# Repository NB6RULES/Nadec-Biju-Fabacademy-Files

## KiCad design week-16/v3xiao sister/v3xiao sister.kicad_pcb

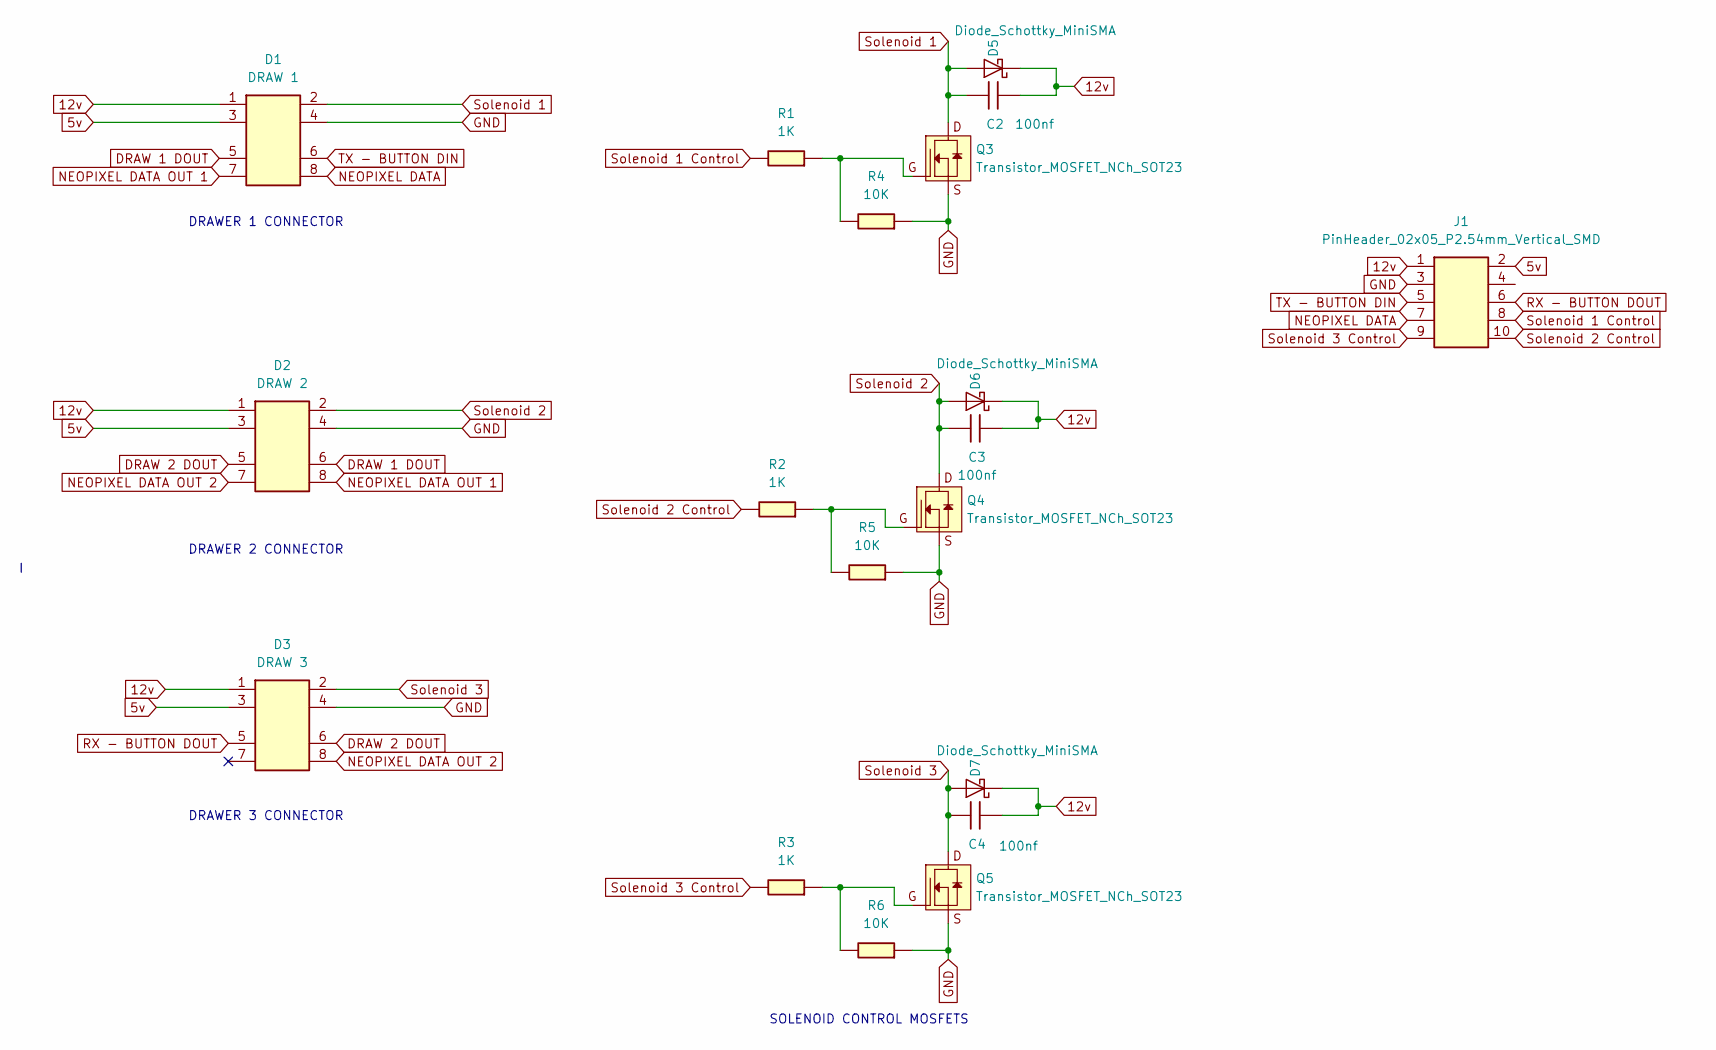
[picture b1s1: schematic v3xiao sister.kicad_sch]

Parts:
C2, C3, C4: 100nf; C_1206
D1: DRAW 1; PinHeader_02x04_P2.54mm_Vertical_SMD
D2: DRAW 2; PinHeader_02x04_P2.54mm_Vertical_SMD
D3: DRAW 3; PinHeader_02x04_P2.54mm_Vertical_SMD
D5, D6, D7: Diode_Schottky_MiniSMA
J1: PinHeader_02x05_P2.54mm_Vertical_SMD
Q3, Q4, Q5: Transistor_MOSFET_NCh_SOT23; SOT-23-3
R1, R2, R3: 1K; R_1206
R4, R5, R6: 10K; R_1206

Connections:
5v: D1.3, D2.3, D3.3, J1.2
12v: C2.2, C3.2, C4.2, D1.1, D2.1, D3.1, D5.1 (K), D6.1 (K), D7.1 (K), J1.1
DRAW 1 DOUT: D1.5, D2.6
DRAW 2 DOUT: D2.5, D3.6
GND: D1.4, D2.4, D3.4, J1.3, Q3.2 (S), Q4.2 (S), Q5.2 (S), R4.2, R5.2, R6.2
NEOPIXEL DATA: D1.8, J1.7
NEOPIXEL DATA OUT 1: D1.7, D2.8
NEOPIXEL DATA OUT 2: D2.7, D3.8
unnamed: Q3.1 (G), R1.2, R4.1
unnamed: Q4.1 (G), R2.2, R5.1
unnamed: Q5.1 (G), R3.2, R6.1
RX - BUTTON DOUT: D3.5, J1.6
Solenoid 1: C2.1, D1.2, D5.2 (A), Q3.3 (D)
Solenoid 1 Control: J1.8, R1.1
Solenoid 2: C3.1, D2.2, D6.2 (A), Q4.3 (D)
Solenoid 2 Control: J1.10, R2.1
Solenoid 3: C4.1, D3.2, D7.2 (A), Q5.3 (D)
Solenoid 3 Control: J1.9, R3.1
TX - BUTTON DIN: D1.6, J1.5

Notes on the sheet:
DRAWER 1 CONNECTOR
SOLENOID CONTROL MOSFETS
DRAWER 3 CONNECTOR
DRAWER 2 CONNECTOR

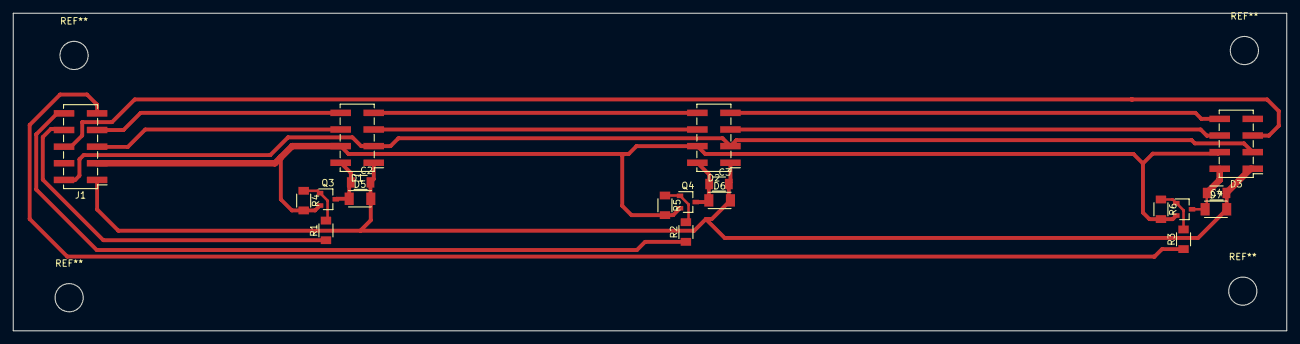
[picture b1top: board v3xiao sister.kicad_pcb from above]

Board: 2 copper layers, 194.5 x 48.5 mm, 19 parts (0 on the bottom side), 19 nets.

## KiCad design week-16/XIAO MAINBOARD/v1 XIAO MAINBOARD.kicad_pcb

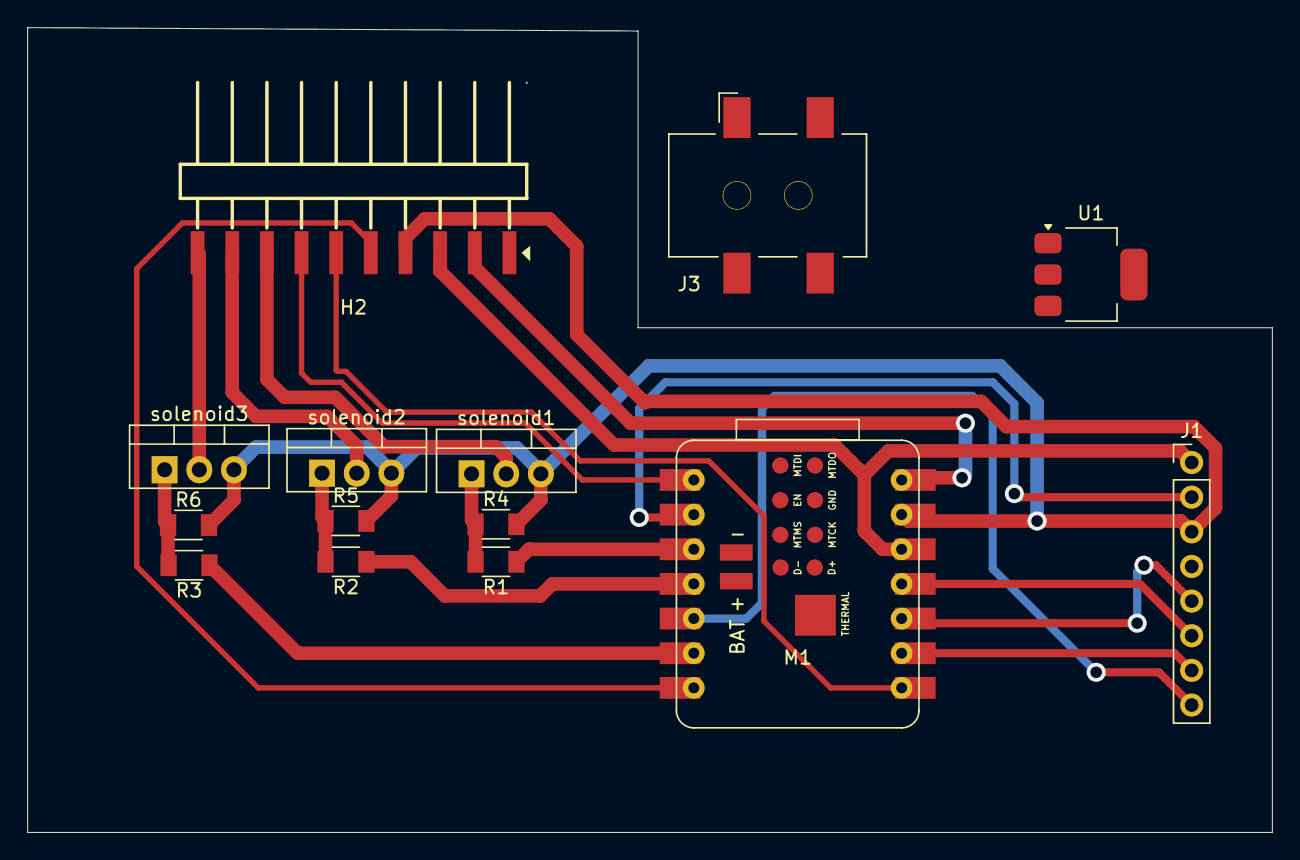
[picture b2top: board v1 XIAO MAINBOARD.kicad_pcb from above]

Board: 2 copper layers, 91.2 x 59.0 mm, 14 parts (0 on the bottom side), 20 nets.

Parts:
H2: HX PZ2.54-1X10P WT; HDR-SMD_10P-P2.54-H-M-W13.3-N
J1: PinHeader_01x08_P2.54mm_Vertical_THT_D1mm
J3: Conn_PWRJack_2x5.5mm_CUIDevices_PJ-002AH-SMT-TR; CUIDevices_PJ-002AH-SMT-TR_PWRJack_2x5.5mm
M1: Module_XIAO-ESP32S3; SeeedStudio_XIAO_ESP32S3
R1, R2, R3: 1K; R_1206
R4, R5, R6: 10K; R_1206
U1: AMS1117; SOT-223-3_TabPin2
solenoid1, solenoid2, solenoid3: IRLZ44N; TO-220-3_Vertical

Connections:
3.3v: H2.3, J1.1, M1.12 (3V3)
5v: H2.2, M1.14 (5V)
GND: H2.4, J1.3, M1.13 (GND), R4.2, R5.2, R6.2, solenoid1.3 (S), solenoid2.3 (S), solenoid3.3 (S)
MISO: J1.5, M1.10 (D9)
MOSI: J1.6, M1.11 (D10)
NEOPIXEL DATA: H2.7, M1.1 (D0)
unnamed: R1.2, R4.1, solenoid1.1 (G)
unnamed: R2.2, R5.1, solenoid2.1 (G)
unnamed: R3.2, R6.1, solenoid3.1 (G)
RST: J1.2, M1.2 (D1)
RX - BUTTON DOUT: H2.6, M1.8 (D7)
SCK: J1.7, M1.9 (D8)
SDA: J1.8, M1.5 (D4)
Solenoid 1: H2.8, solenoid1.2 (D)
Solenoid 1 Control: M1.3 (D2), R1.1
Solenoid 2: H2.9, solenoid2.2 (D)
Solenoid 2 Control: M1.4 (D3), R2.1
Solenoid 3: H2.10, solenoid3.2 (D)
Solenoid 3 Control: M1.6 (D5), R3.1
TX - BUTTON DIN: H2.5, M1.7 (D6)

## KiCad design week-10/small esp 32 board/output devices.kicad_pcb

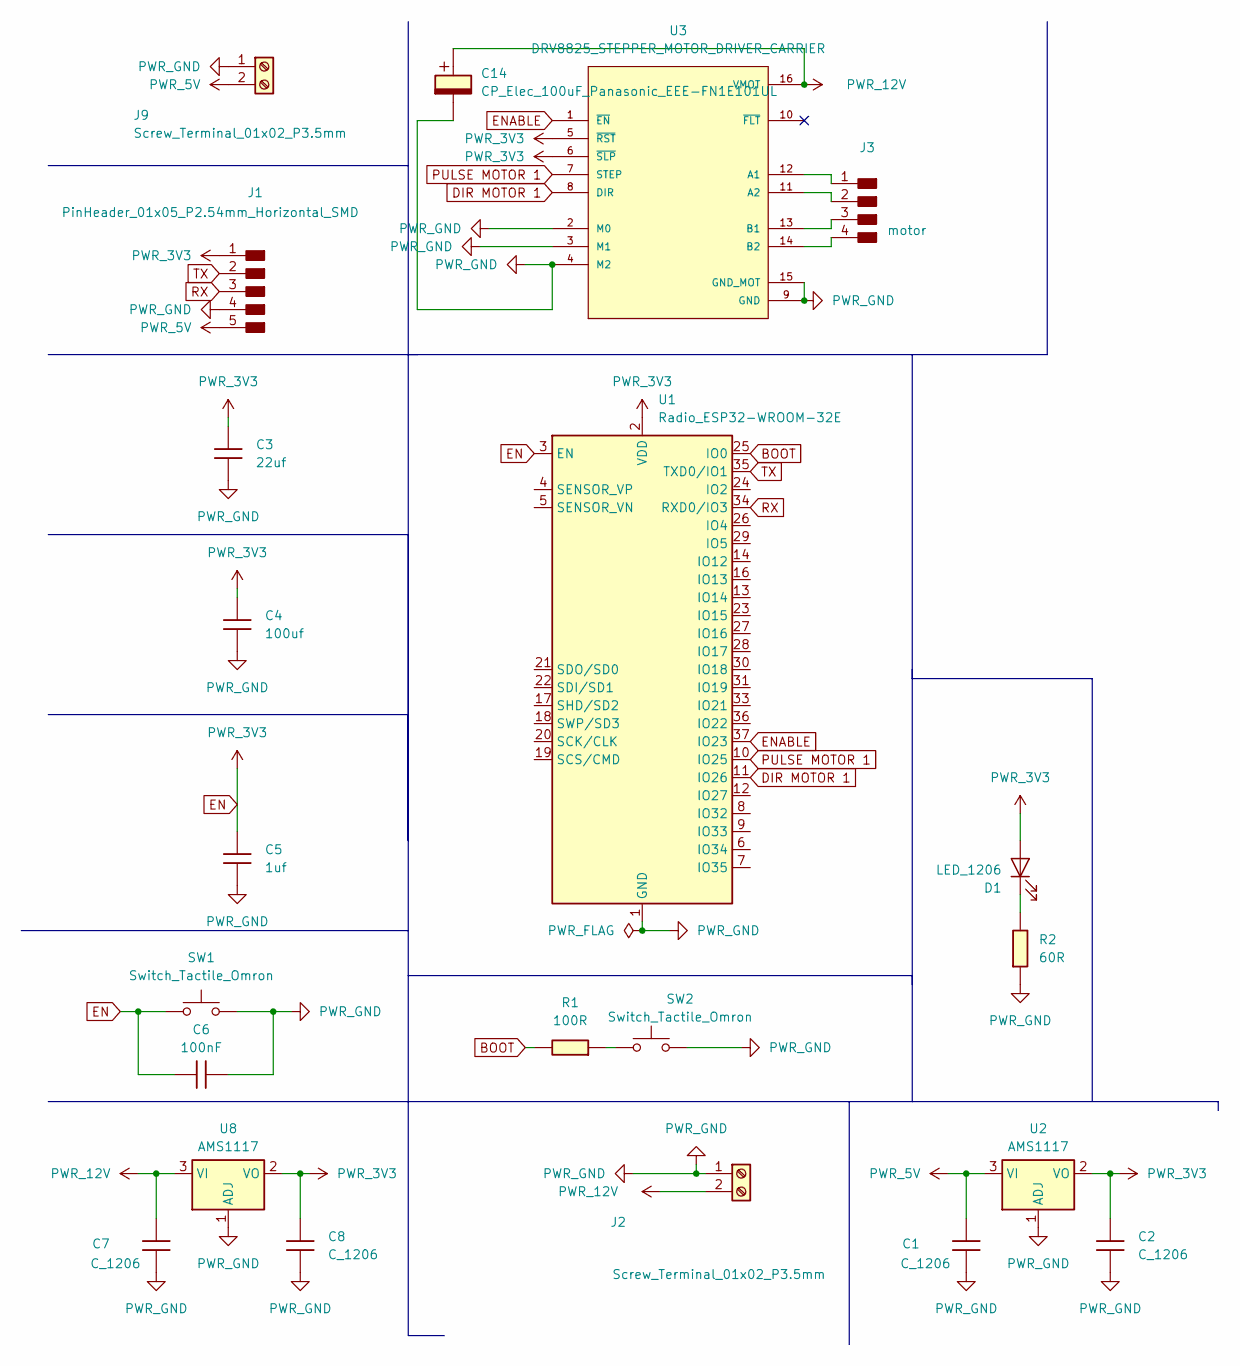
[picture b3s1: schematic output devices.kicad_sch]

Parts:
C1, C2, C7, C8: C_1206
C3: 22uf; C_1206
C4: 100uf; C_1206
C5: 1uf; C_1206
C6: 100nF; C_1206
C14: CP_Elec_100uF_Panasonic_EEE-FN1E101UL; CP_Elec_8x10
D1: LED_1206
J1: PinHeader_01x05_P2.54mm_Horizontal_SMD
J2, J9: Screw_Terminal_01x02_P3.5mm; TerminalBlock_OnShore_1x02_P3.50mm_Horizontal
J3: motor; PinHeader_01x04_P2.54mm_Horizontal_SMD
R1: 100R; R_1206
R2: 60R; R_1206
SW1, SW2: Switch_Tactile_Omron; Button_Omron_B3SN_6.0x6.0mm
U1: Radio_ESP32-WROOM-32E; ESP32-WROOM-32E
U2, U8: AMS1117; SOT-223-3_TabPin2
U3: DRV8825_STEPPER_MOTOR_DRIVER_CARRIER; IC_DRV8825_STEPPER_MOTOR_DRIVER_CARRIER

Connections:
BOOT: R1.1, U1.25 (IO0)
DIR MOTOR 1: U1.11 (IO26), U3.8 (DIR)
EN: C2.1, C3.1, C4.1, C5.1, C6.1, C8.1, D1.2 (A), J1.1, SW1.1, U1.2 (VDD), U1.3 (EN), U2.2 (VO), U3.5 (~RST), U3.6 (~SLP), U8.2 (VO)
ENABLE: U1.37 (IO23), U3.1 (~EN)
unnamed: D1.1 (K), R2.1
unnamed: J3.1, U3.12 (A1)
unnamed: J3.2, U3.11 (A2)
unnamed: J3.3, U3.13 (B1)
unnamed: J3.4, U3.14 (B2)
unnamed: R1.2, SW2.1
PULSE MOTOR 1: U1.10 (IO25), U3.7 (STEP)
PWR_5V: C1.1, J1.5, J9.2, U2.3 (VI)
PWR_12V: C7.1, C14.1, J2.2, U3.16 (VMOT), U8.3 (VI)
PWR_GND: C1.2, C2.2, C3.2, C4.2, C5.2, C6.2, C7.2, C8.2, C14.2, J1.4, J2.1, J9.1, R2.2, SW1.2, SW2.2, U1.1 (GND), U1.15 (GND), U1.38 (GND), U1.39 (GND), U2.1 (ADJ), U3.2 (M0), U3.3 (M1), U3.4 (M2), U3.9 (GND), U3.15 (GND_MOT), U8.1 (ADJ)
RX: J1.3, U1.34 (RXD0/IO3)
TX: J1.2, U1.35 (TXD0/IO1)

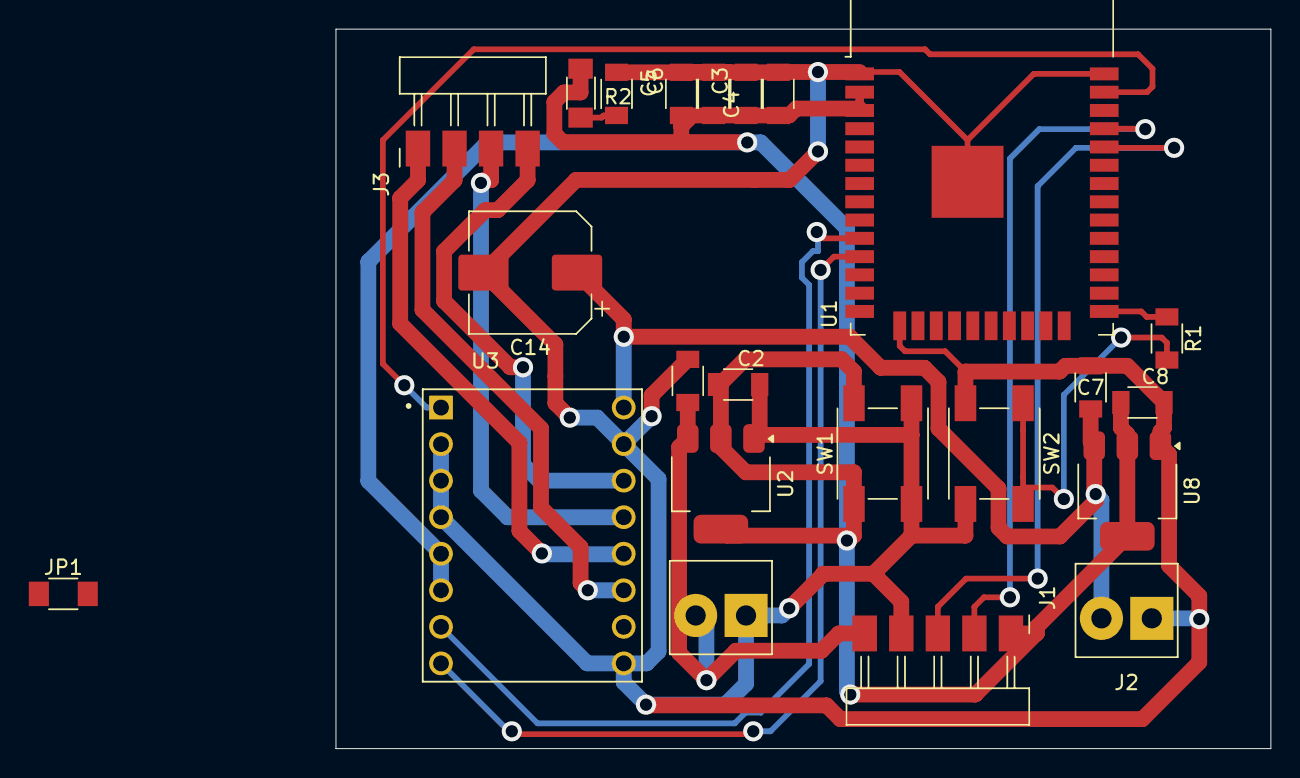
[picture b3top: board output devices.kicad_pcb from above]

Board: 2 copper layers, 65.0 x 50.0 mm, 23 parts (0 on the bottom side), 16 nets.

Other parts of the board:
JP1: Jumper_2_Open; Jumper_1206

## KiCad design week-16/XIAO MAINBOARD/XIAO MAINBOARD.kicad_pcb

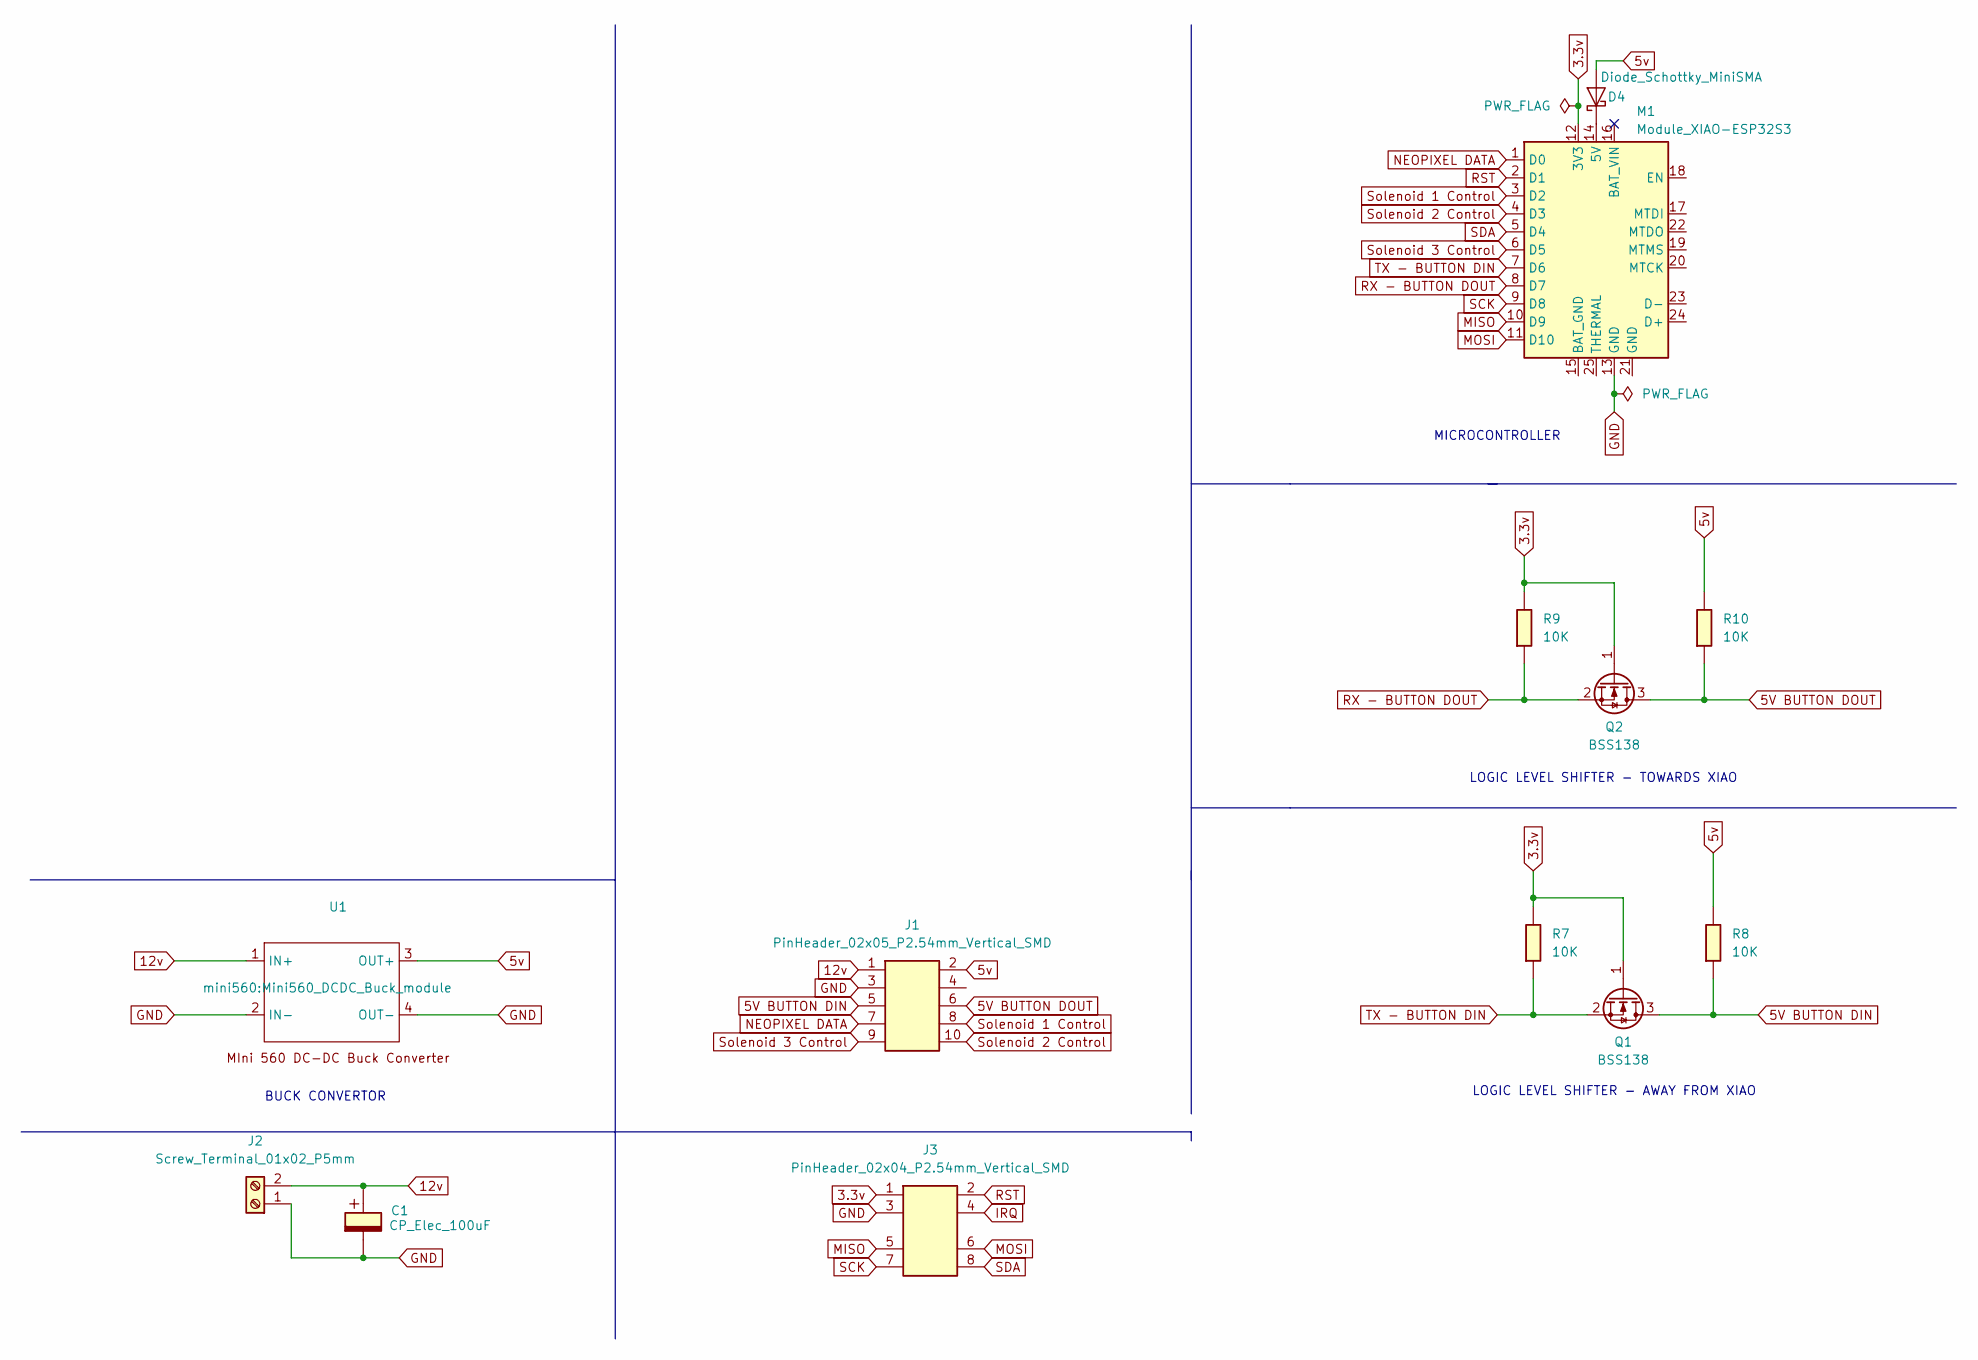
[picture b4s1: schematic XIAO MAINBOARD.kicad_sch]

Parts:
C1: CP_Elec_100uF; CP_Elec_100uF_Panasonic_EEE-FN1E101UL
D4: Diode_Schottky_MiniSMA
J1: PinHeader_02x05_P2.54mm_Vertical_SMD
J2: Screw_Terminal_01x02_P5mm; TerminalBlock_OnShore_1x02_P5.00mm_Horizontal
J3: PinHeader_02x04_P2.54mm_Vertical_SMD
M1: Module_XIAO-ESP32S3; SeeedStudio_XIAO_ESP32S3
Q1, Q2: BSS138; SOT-23
R7, R8, R9, R10: 10K; R_1206
U1: Mini560_DCDC_Buck_module

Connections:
3.3v: J3.1, M1.12 (3V3), Q1.1 (G), Q2.1 (G), R7.1, R9.1
5V BUTTON DIN: J1.5, Q1.3 (D), R8.2
5V BUTTON DOUT: J1.6, Q2.3 (D), R10.2
5v: D4.2 (A), J1.2, R8.1, R10.1, U1.3 (OUT+)
12v: C1.1, J1.1, J2.2, U1.1 (IN+)
GND: C1.2, J1.3, J2.1, J3.3, M1.13 (GND), U1.2 (IN-), U1.4 (OUT-)
IRQ: J3.4
MISO: J3.5, M1.10 (D9)
MOSI: J3.6, M1.11 (D10)
NEOPIXEL DATA: J1.7, M1.1 (D0)
unnamed: D4.1 (K), M1.14 (5V)
RST: J3.2, M1.2 (D1)
RX - BUTTON DOUT: M1.8 (D7), Q2.2 (S), R9.2
SCK: J3.7, M1.9 (D8)
SDA: J3.8, M1.5 (D4)
Solenoid 1 Control: J1.8, M1.3 (D2)
Solenoid 2 Control: J1.10, M1.4 (D3)
Solenoid 3 Control: J1.9, M1.6 (D5)
TX - BUTTON DIN: M1.7 (D6), Q1.2 (S), R7.2

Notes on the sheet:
MICROCONTROLLER
LOGIC LEVEL SHIFTER - TOWARDS XIAO
LOGIC LEVEL SHIFTER - AWAY FROM XIAO
BUCK CONVERTOR

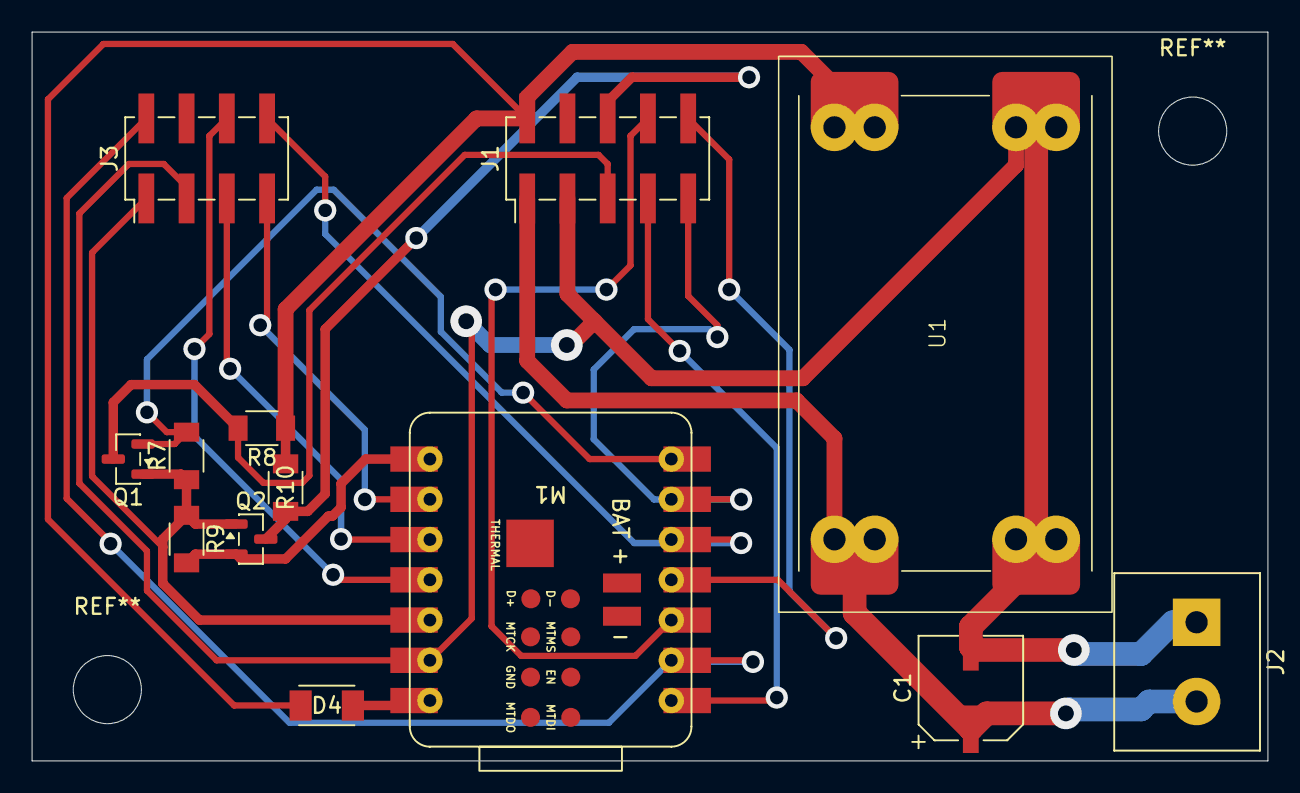
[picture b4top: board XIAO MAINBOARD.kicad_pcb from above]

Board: 2 copper layers, 78.0 x 46.0 mm, 13 parts (0 on the bottom side), 18 nets.

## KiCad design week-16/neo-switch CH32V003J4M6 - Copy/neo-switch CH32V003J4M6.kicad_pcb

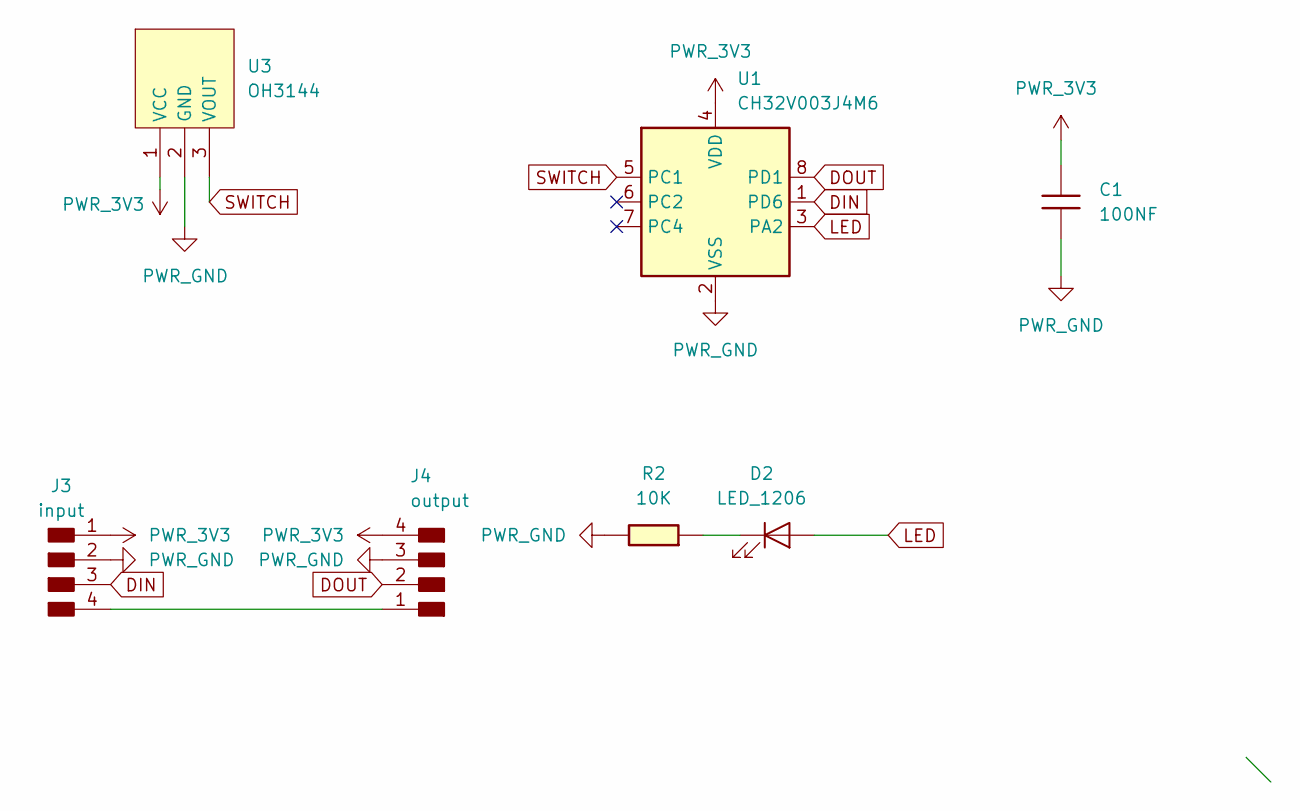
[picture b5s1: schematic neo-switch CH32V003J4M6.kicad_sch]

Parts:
C1: 100NF; C_1206
D2: LED_1206
J3: input; PinHeader_01x04_P2.54mm_Horizontal_SMD
J4: output; PinHeader_01x04_P2.54mm_Horizontal_SMD
R2: 10K; R_1206
U1: CH32V003J4M6; SO-8_3.9x4.9mm_P1.27mm
U3: OH3144; TO-92-3_L4.9-W3.7-P1.27-L; MPN OH3144; LCSC Part C81152

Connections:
DIN: J3.3, U1.1 (PD6)
DOUT: J4.2, U1.8 (PD1)
LED: D2.2 (A), U1.3 (PA2)
unnamed: D2.1 (K), R2.2
unnamed: J3.4, J4.1
PWR_3V3: C1.1, J3.1, J4.4, U1.4 (VDD), U3.1 (VCC)
PWR_GND: C1.2, J3.2, J4.3, R2.1, U1.2 (VSS), U3.2 (GND)
SWITCH: U1.5 (PC1), U3.3 (VOUT)

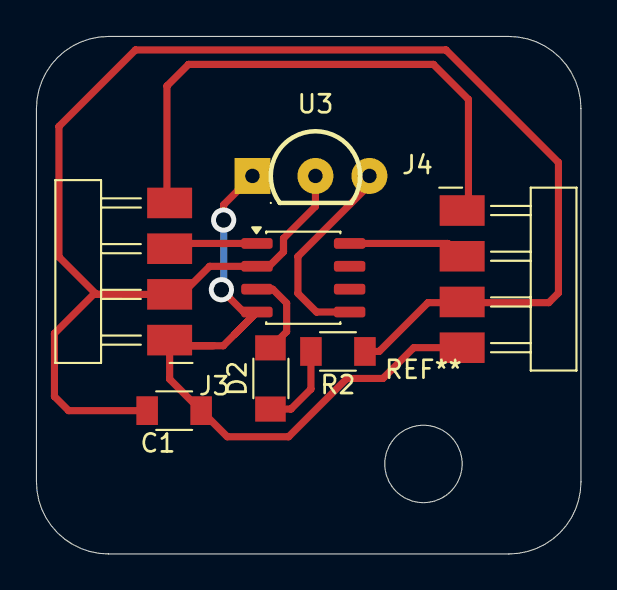
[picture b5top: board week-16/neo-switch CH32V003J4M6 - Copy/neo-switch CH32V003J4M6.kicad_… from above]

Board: 2 copper layers, 30.2 x 28.8 mm, 7 parts (0 on the bottom side), 8 nets.

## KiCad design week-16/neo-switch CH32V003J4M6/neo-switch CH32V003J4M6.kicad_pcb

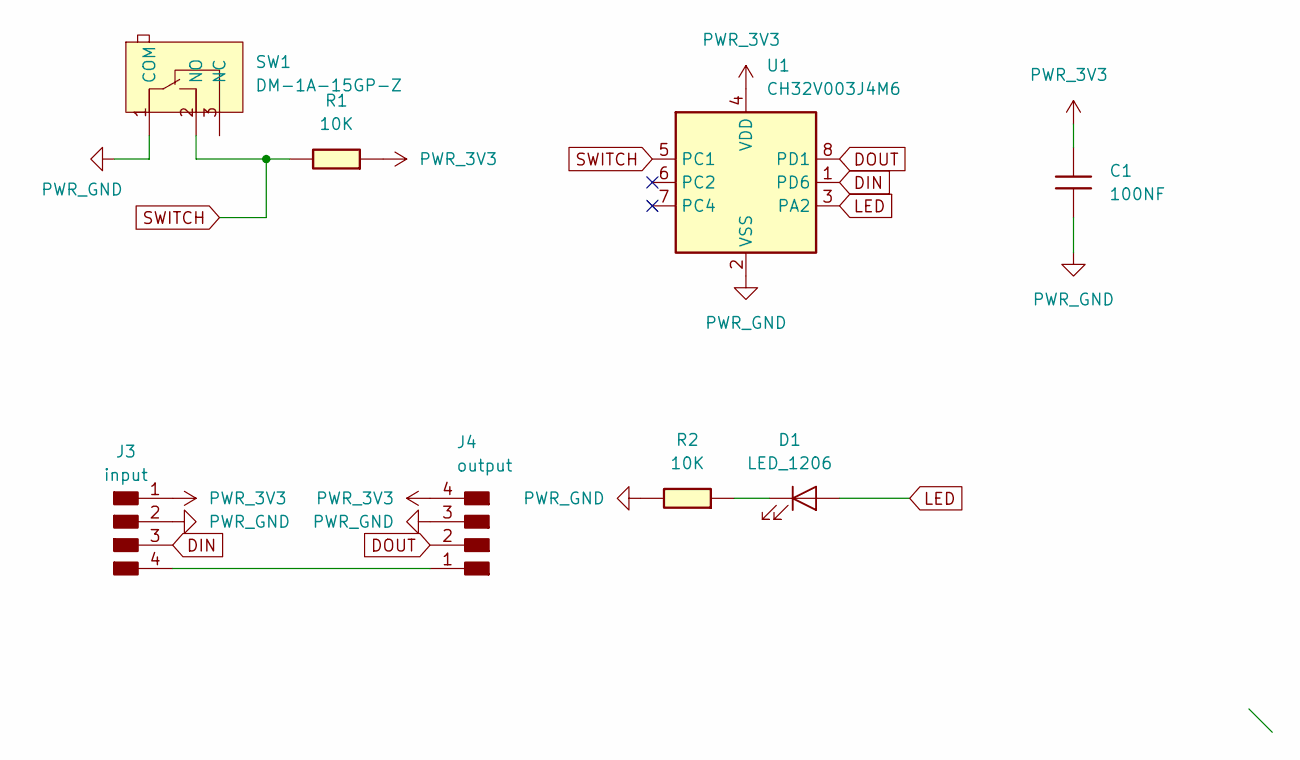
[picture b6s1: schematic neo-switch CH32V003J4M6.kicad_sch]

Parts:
C1: 100NF; C_1206
D1: LED_1206
J3: input; PinHeader_01x04_P2.54mm_Horizontal_SMD
J4: output; PinHeader_01x04_P2.54mm_Horizontal_SMD
R1, R2: 10K; R_1206
SW1: DM-1A-15GP-Z; SW-TH_3P-L12.8-W5.8-P5.08; MPN DM-1A-15GP-Z; LCSC Part C22459518
U1: CH32V003J4M6; SO-8_3.9x4.9mm_P1.27mm

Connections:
DIN: J3.3, U1.1 (PD6)
DOUT: J4.2, U1.8 (PD1)
LED: D1.2 (A), U1.3 (PA2)
unnamed: D1.1 (K), R2.2
unnamed: J3.4, J4.1
PWR_3V3: C1.1, J3.1, J4.4, R1.2, U1.4 (VDD)
PWR_GND: C1.2, J3.2, J4.3, R2.1, SW1.1 (COM), U1.2 (VSS)
SWITCH: R1.1, SW1.2 (NO), U1.5 (PC1)

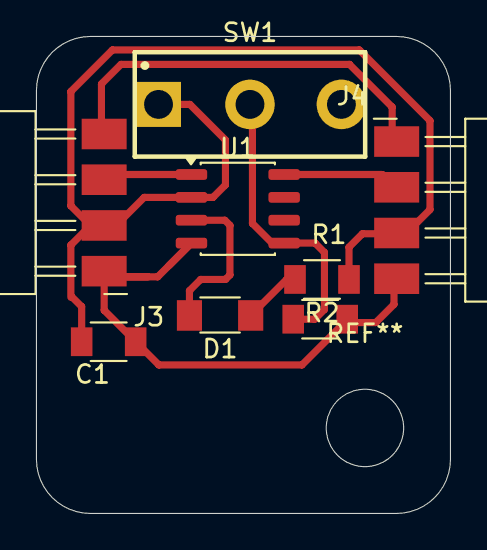
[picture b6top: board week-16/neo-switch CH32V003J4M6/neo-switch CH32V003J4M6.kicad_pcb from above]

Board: 2 copper layers, 23.0 x 26.5 mm, 8 parts (0 on the bottom side), 8 nets.

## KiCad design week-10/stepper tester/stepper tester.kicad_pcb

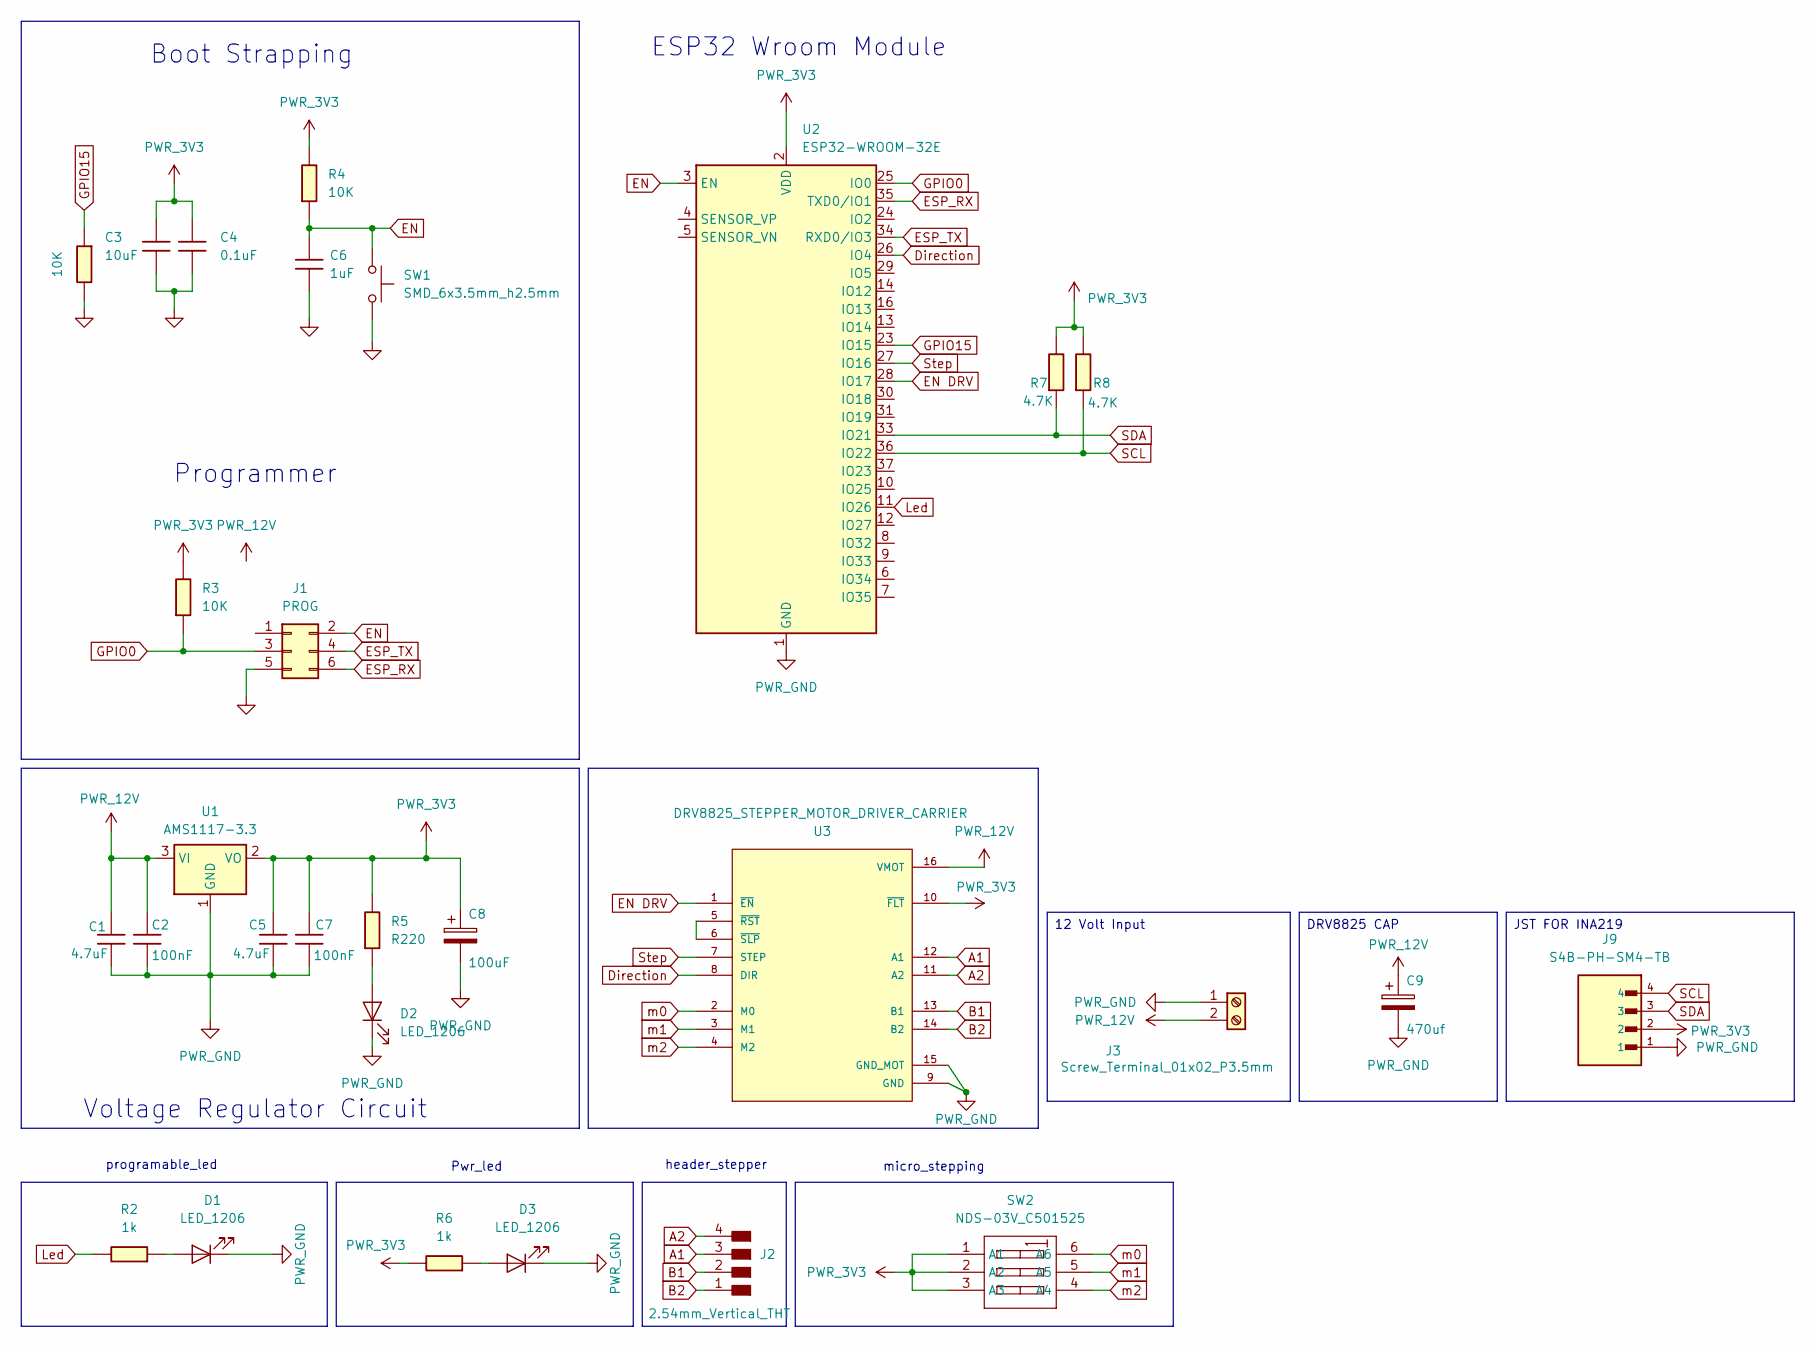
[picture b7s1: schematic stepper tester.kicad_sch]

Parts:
C1, C5: 4.7uF; C_1206_3216Metric_Pad1.33x1.80mm_HandSolder
C2, C7: 100nF; C_1206_3216Metric_Pad1.33x1.80mm_HandSolder
C3: 10uF; C_1206_3216Metric_Pad1.33x1.80mm_HandSolder
C4: 0.1uF; C_1206_3216Metric_Pad1.33x1.80mm_HandSolder
C6: 1uF; C_1206_3216Metric_Pad1.33x1.80mm_HandSolder
C8: 100uF; CP_Elec_10x10
C9: 470uf; CP_Elec_10x10
D1, D2, D3: LED_1206
J1: PROG; PinHeader_2x03_P2.54mm_Vertical_SMD
J2: 2.54mm_Vertical_THT; PinHeader_01x04_P2.54mm_Vertical_THT_D1.4mm
J3: Screw_Terminal_01x02_P3.5mm; TerminalBlock_OnShore_1x02_P3.50mm_Horizontal
J9: S4B-PH-SM4-TB; JST_S4B-PH-SM4-TB
R1, R3, R4: 10K; R_1206_3216Metric_Pad1.30x1.75mm_HandSolder
R2, R6: 1k; R_1206
R5: R220; R_1206_3216Metric_Pad1.30x1.75mm_HandSolder
R7, R8: 4.7K; R_1206_3216Metric_Pad1.30x1.75mm_HandSolder
SW1: SMD_6x3.5mm_h2.5mm; SW_Push_SPST_NO_Alps_SKRK; Mfg Part# 8-004 SMD Button 8x3.6mm Height=2.5mm
SW2: NDS-03V_C501525; SW-TH_6P-L9.2-W9.9-P2.54-LS7.6; MPN NDS-03V; LCSC Part C501525
U1: AMS1117-3.3; SOT-223-3_TabPin2
U2: ESP32-WROOM-32E; ESP32-WROOM-32D
U3: DRV8825_STEPPER_MOTOR_DRIVER_CARRIER; IC_DRV8825_STEPPER_MOTOR_DRIVER_CARRIER

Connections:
EN DRV: U2.28 (IO17), U3.1 (~EN)
A1: J2.3, U3.12 (A1)
A2: J2.4, U3.11 (A2)
B1: J2.2, U3.13 (B1)
B2: J2.1, U3.14 (B2)
Direction: U2.26 (IO4), U3.8 (DIR)
EN: C6.1, J1.2, R4.2, SW1.1, U2.3 (EN)
ESP_RX: J1.6, U2.35 (TXD0/IO1)
ESP_TX: J1.4, U2.34 (RXD0/IO3)
GPIO0: J1.3, R3.2, U2.25 (IO0)
GPIO15: R1.2, U2.23 (IO15)
Led: R2.1, U2.11 (IO26)
unnamed: D1.2 (A), R2.2
unnamed: D2.2 (A), R5.2
unnamed: D3.2 (A), R6.2
unnamed: U3.5 (~RST), U3.6 (~SLP)
PWR_3V3: C3.1, C4.1, C5.1, C7.1, C8.1, J9.2, R3.1, R4.1, R5.1, R6.1, R7.1, R8.1, SW2.1 (A1), SW2.2 (A2), SW2.3 (A3), U1.2 (VO), U2.2 (VDD), U3.10 (~FLT)
PWR_12V: C1.1, C2.1, C9.1, J3.2, U1.3 (VI), U3.16 (VMOT)
PWR_GND: C1.2, C2.2, C3.2, C4.2, C5.2, C6.2, C7.2, C8.2, C9.2, D1.1 (K), D2.1 (K), D3.1 (K), J1.5, J3.1, J9.1, R1.1, SW1.2, U1.1 (GND), U2.1 (GND), U2.15 (GND), U2.38 (GND), U2.39 (GND), U3.9 (GND), U3.15 (GND_MOT)
SCL: J9.4, R8.2, U2.36 (IO22)
SDA: J9.3, R7.2, U2.33 (IO21)
Step: U2.27 (IO16), U3.7 (STEP)
m0: SW2.6 (A6), U3.2 (M0)
m1: SW2.5 (A5), U3.3 (M1)
m2: SW2.4 (A4), U3.4 (M2)

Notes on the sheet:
ESP32 Wroom Module
programable_led
Voltage Regulator Circuit
Boot Strapping
Pwr_led
Programmer
header_stepper
micro_stepping
JST FOR INA219
12 Volt Input
DRV8825 CAP

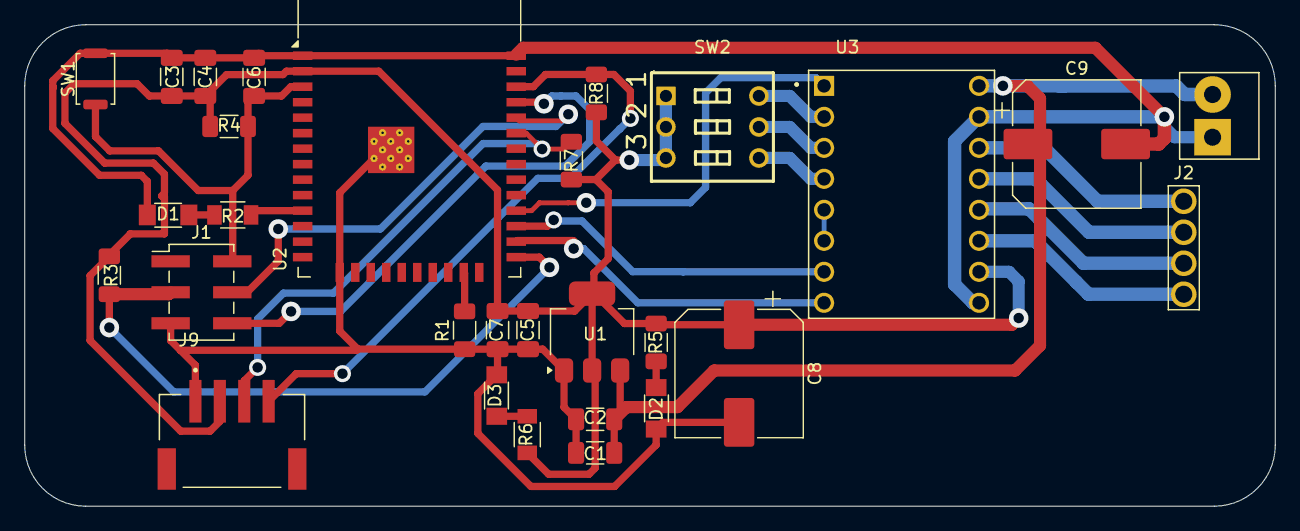
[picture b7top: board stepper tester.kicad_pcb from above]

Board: 2 copper layers, 102.5 x 39.5 mm, 29 parts (0 on the bottom side), 25 nets.

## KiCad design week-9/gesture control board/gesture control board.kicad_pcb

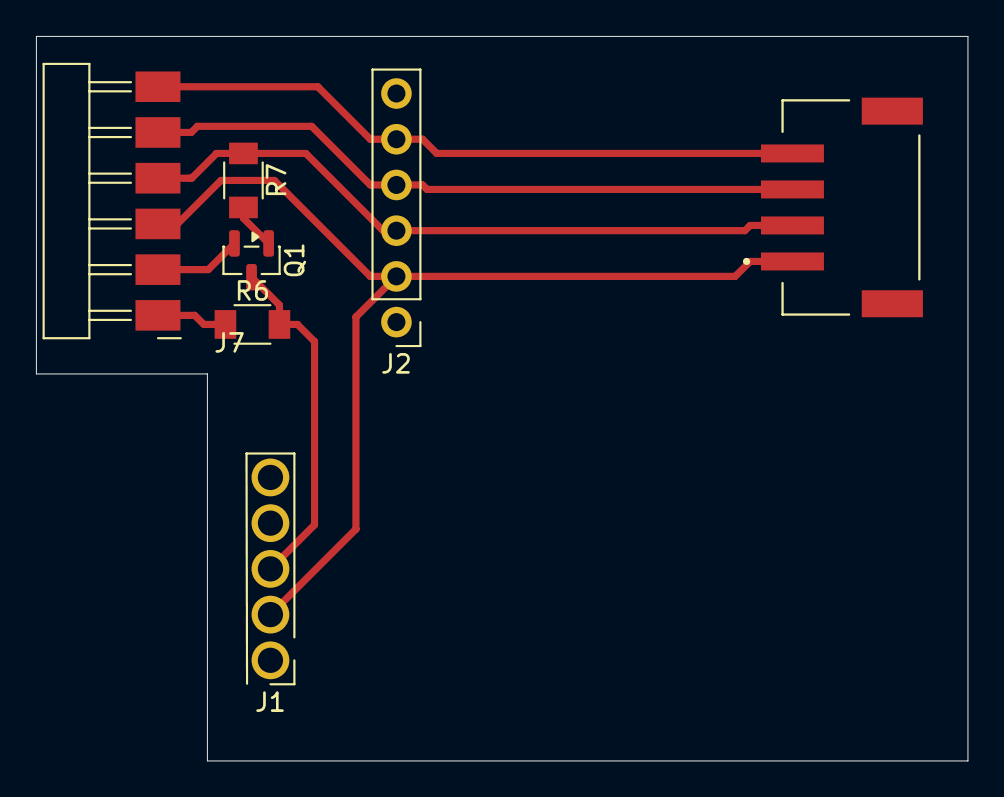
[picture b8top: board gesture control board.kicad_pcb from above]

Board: 2 copper layers, 51.8 x 40.2 mm, 7 parts (0 on the bottom side), 8 nets.

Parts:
J1: RCWL-0516; PinHeader_01x05_P2.54mm_Vertical_THT_D1.4mm
J2: APDS-9960; PinHeader_01x06_P2.54mm_Vertical_THT_D1mm
J3: VL53L0X; JST_S4B-PH-SM4-TB
J7: PinHeader_01x06_P2.54mm_Horizontal_SMD
Q1: BSS138; SOT-23
R6, R7: 10k; R_1206

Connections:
3.3v LOGIC OUT: J7.2, Q1.2 (S)
5V IN: J7.1, R6.1
5v LOGIC OUT: J1.3, Q1.3 (D), R6.2
GND: J1.2, J2.2, J3.1, J7.3
unnamed: Q1.1 (G), R7.2
SCL: J2.5, J3.4, J7.6
SDA: J2.4, J3.3, J7.5
VCC: J2.3, J3.2, J7.4, R7.1

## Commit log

2026-02-04 added tinkercad file
2026-02-10 week3 files added
2026-02-11 week three final data added
2026-02-13 week4 first code
2026-02-14 gameboy 8:14 14/2/26
2026-02-15 gameboy till minesweeper
2026-02-16 final code before firebase
2026-02-25 week 5 files
2026-03-05 week-6 updated
2026-03-11 week-7
2026-03-11 week-7.1
2026-04-05 week-9
2026-06-23 weeks
